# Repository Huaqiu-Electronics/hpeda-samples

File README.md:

# hpeda-samples
HQEDA Samples

## Boards

| 路径 | 说明 |
|------|------|
| [Boards](./Boards/README.md) | 简易 V5 `.hqpcbx`（01–11：基础/盲孔/槽孔/圆弧板框/差分对等） |

## SDK

| 路径 | 说明 |
|------|------|
| [sdk](./sdk/README.md) | Python / JavaScript / Go Flight IPC 读写示例（默认用 `Boards/hqpcbx`） |

## Scripts

| 路径 | 说明 |
|------|------|
| [Scripts](./Scripts/README.md) | 控制台一键脚本（Lisp / Js / Python / Go） |
| [Scripts/Lisp](./Scripts/Lisp/README.md) | HQ-LISP 样例（需 `PCB_ENABLE_LISP=ON`） |

## Plugins

| 路径 | 说明 |
|------|------|
| [Plugins](./Plugins/README.md) | 多语言插件最小示例（Js / Python / Java / Go） |

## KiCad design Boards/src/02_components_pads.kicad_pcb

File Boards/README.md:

# Boards — 简易 V5 样板（`.hqpcbx` / `.hqpcb`）

覆盖基本与进阶 PCB 元素的小样板，便于打开验证、导入回归与教学演示。  
**SDK / 脚本示例默认使用 `hqpcbx/*.hqpcbx`（文本工程）。**

## 目录

| 路径 | 说明 |
|------|------|
| `src/*.kicad_pcb` | 手写 KiCad 源（权威可编辑稿） |
| `hqpcbx/*.hqpcbx` | 文本工程（SDK 样例默认；`convert_to_hqpcb.sh --hqpcbx-only`） |
| `hqpcb/*.hqpcb` | SQLite 工程（可选，`convert_to_hqpcb.sh`） |
| `convert_to_hqpcb.sh` | 批量 `HQPCB_CLI convert`（`--hqpcbx` / `--hqpcbx-only`） |

## 样板一览

### 基础

| 文件 | 覆盖元素 |
|------|----------|
| `01_tracks_vias` | 板框、网络、直线走线、过孔、丝印文字 |
| `02_components_pads` | SMD/插件封装、焊盘、位号/值、短走线 |
| `03_zones_graphics` | 铺铜、丝印线/圆/弧/多边形、文字 |
| `04_all_basics` | 上述元素合一的综合小板 |

### 进阶

| 文件 | 覆盖元素 |
|------|----------|
| `05_arc_tracks_vias` | 圆弧走线、4 层板、microvia、贯通过孔 |
| `06_keepout_netclass` | 禁布区 keepout、net_class（含差分）、铺铜 |
| `07_custom_pads_curves` | oval/roundrect/custom 焊盘、安装孔、贝塞尔曲线、填充矩形/圆 |
| `08_blind_bottom` | 盲孔、顶/底面器件、镜像丝印 |
| `09_slots_thermals` | 椭圆槽孔、NPTH、zone_connect/热焊盘、铺铜 |
| `10_outline_arcs` | Edge.Cuts 圆弧板框、丝印弧/圆、铺铜 |
| `11_diffpair_route` | USB 差分平行/圆弧走线、net_class、连接器+IC |

## 重新转换

```bash
./Samples/Boards/convert_to_hqpcb.sh --hqpcbx-only   # SDK 样例用（推荐）
./Samples/Boards/convert_to_hqpcb.sh --hqpcbx        # 同时写出 .hqpcb + .hqpcbx
./Samples/Boards/convert_to_hqpcb.sh                 # 仅 .hqpcb
```

第三方直出文本工程也可单文件：

```bash
HQPCB_CLI convert Samples/Boards/src/01_tracks_vias.kicad_pcb Samples/Boards/hqpcbx/01_tracks_vias.hqpcbx
```

## 打开

```bash
project.open /abs/path/to/Samples/Boards/hqpcbx/11_diffpair_route.hqpcbx
project.open /abs/path/to/Samples/Boards/hqpcb/11_diffpair_route.hqpcb
```

亦可直接 `project.open` 对应的 `.kicad_pcb`（走 KiCad 导入插件）。

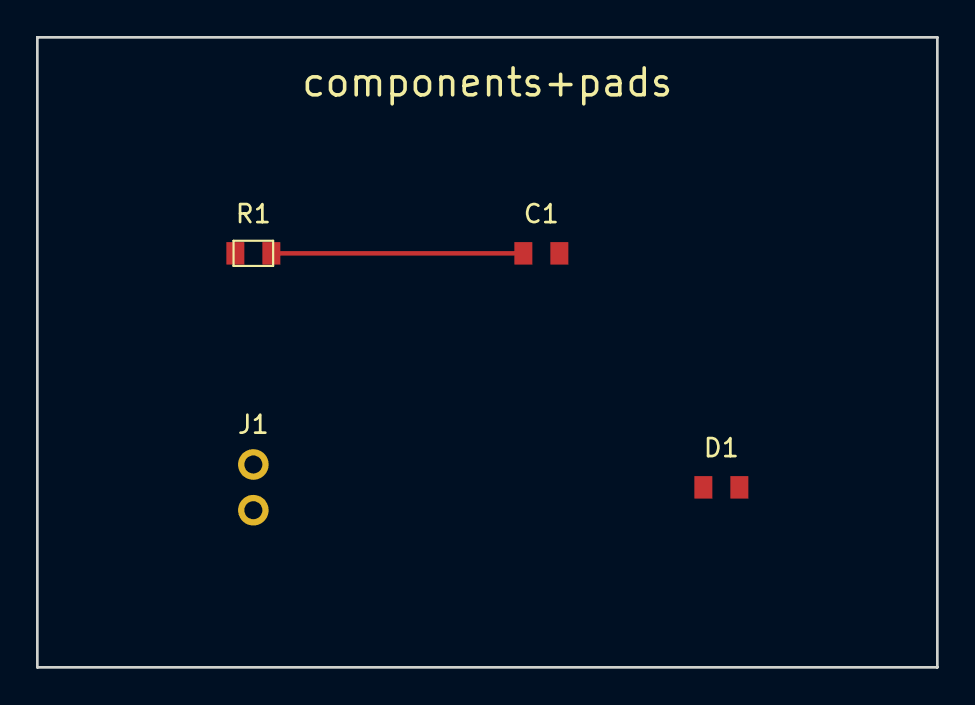
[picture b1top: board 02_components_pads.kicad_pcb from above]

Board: 2 copper layers, 50.0 x 35.0 mm, 4 parts (0 on the bottom side), 3 nets.

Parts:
C1: 100n; C_0805
D1: LED; LED_0805
J1: HDR; PinHeader_1x02
R1: 10k; R_0805

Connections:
GND: C1.2, D1.2, J1.2
NET_A: C1.1, R1.2
VCC: J1.1, R1.1

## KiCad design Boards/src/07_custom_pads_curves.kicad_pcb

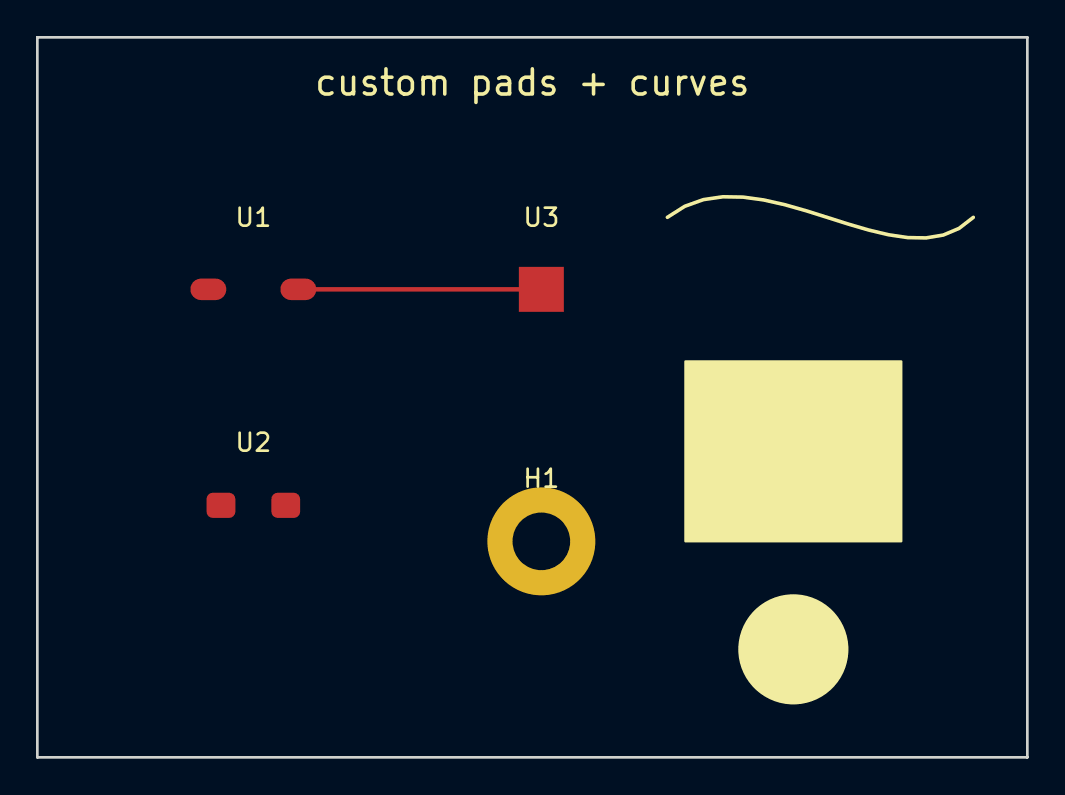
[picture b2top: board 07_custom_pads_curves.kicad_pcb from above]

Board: 2 copper layers, 55.0 x 40.0 mm, 4 parts (0 on the bottom side), 2 nets.

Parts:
H1: M3
U1: OVAL; OvalPad
U2: RRECT; RoundRect
U3: CUSTOM; CustomPoly

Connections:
GND: U1.2, U2.2
SIG_A: U1.1, U3.1
